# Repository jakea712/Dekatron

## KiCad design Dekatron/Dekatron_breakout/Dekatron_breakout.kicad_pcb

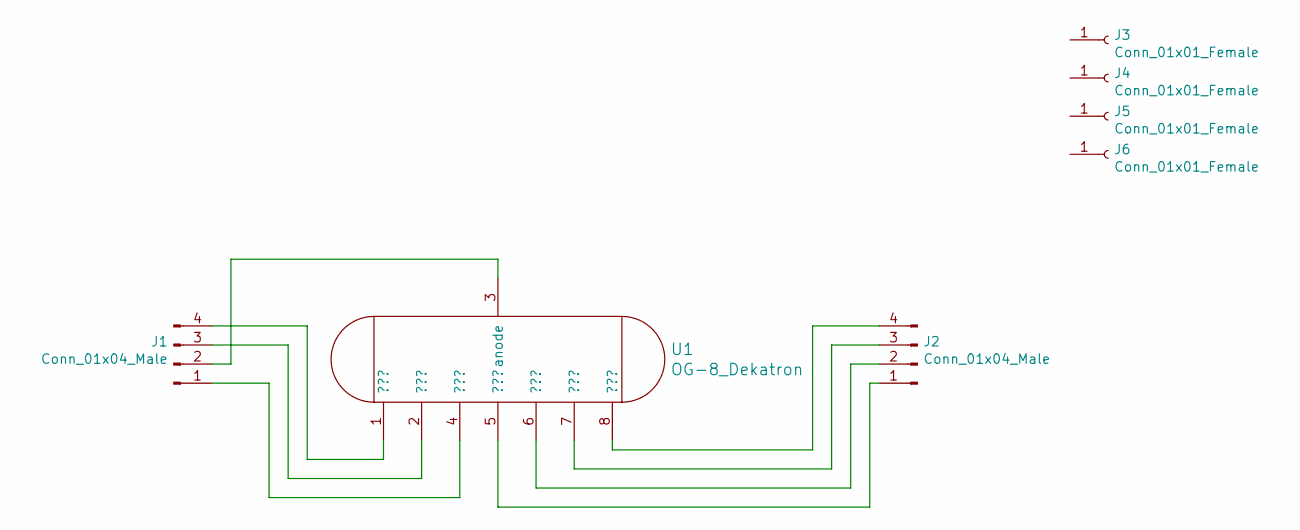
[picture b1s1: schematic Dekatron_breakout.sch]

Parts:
J1, J2: Conn_01x04_Male; PinHeader_1x04_P2.54mm_Vertical
J3, J4, J5, J6: Conn_01x01_Female; MountingHole_3.2mm_M3_ISO7380
U1: OG-8_Dekatron; OG-8 Dekatron

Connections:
unnamed: J1.1, U1.4 (???)
unnamed: J1.2, U1.3 (anode)
unnamed: J1.3, U1.2 (???)
unnamed: J1.4, U1.1 (???)
unnamed: J2.1, U1.5 (???)
unnamed: J2.2, U1.6 (???)
unnamed: J2.3, U1.7 (???)
unnamed: J2.4, U1.8 (???)

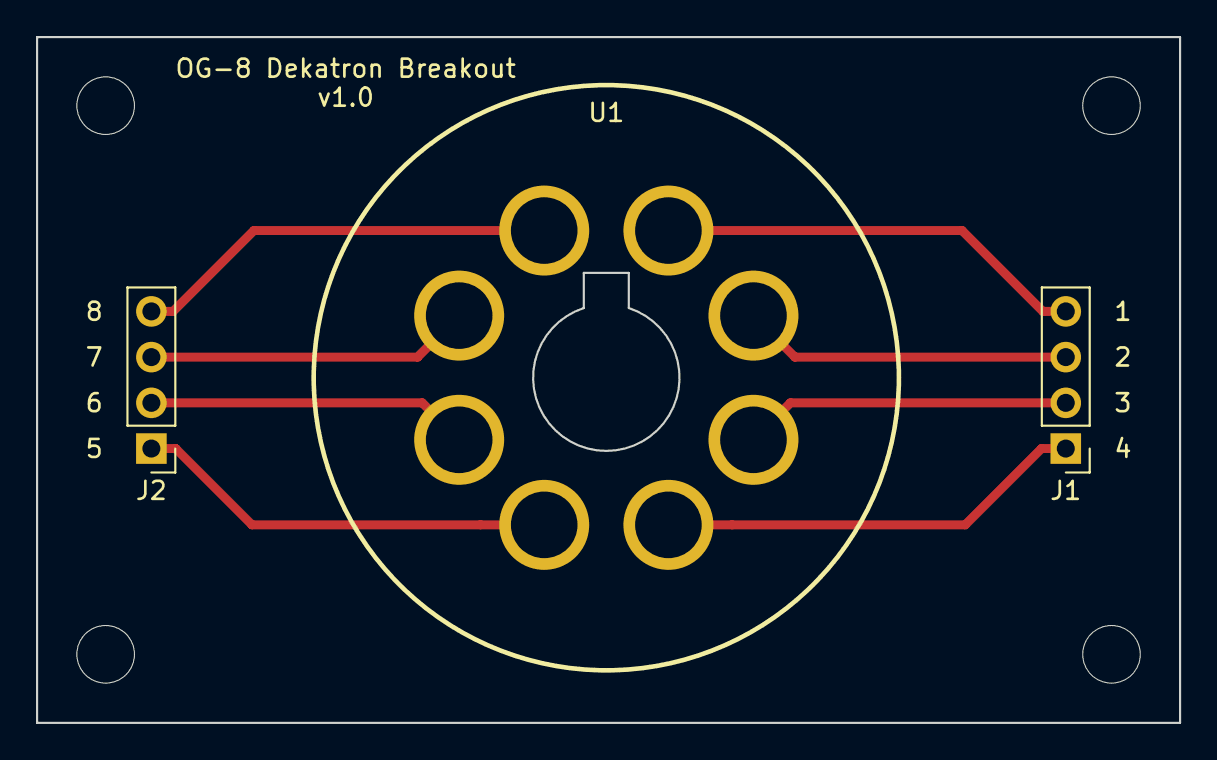
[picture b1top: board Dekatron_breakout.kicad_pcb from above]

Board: 2 copper layers, 63.5 x 38.1 mm, 7 parts (0 on the bottom side), 8 nets.

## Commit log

2020-04-06 Added a breakout board to test the footprint
2020-04-06 Added model for analysing output ripple
2020-04-09 Added some generic boost models
2020-04-22 Developed PSU topology
2020-04-25 Model development
